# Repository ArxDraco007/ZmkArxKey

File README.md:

# ArxKey - A Custom Split Keyboard

## Building a custom wireless split mechanical keyboard from scratch.

## Why did I make this project?
  There are a lot of ill effects of using a non-ergonomic keyboard. Some basic effects happen, such as ulnar deviation (bending wrists outward), forearm pronation (palms facing down), and unnatural extension. It might also get very serious if you have Carpal Tunnel Syndrome (CTS): The median nerve in the wrist is compressed, often due to swollen tendons. It leads to numbness, tingling, and weakened grip strength. As the times change, you will require a keyboard as it becomes an integral part of your everyday life. It is best to have an ergonomic (furniture or equipment that makes it comfortable and effective for people who use it) keyboard, to make sure you enjoy your work.
You can also type very fast. It is also a very fun project to make, and it is also very cool to have your own custom keyboard (split one too).
### PICTURES!!!
The easy part -

The not-so-easy part - 

fusio' - 

## Assembly instructions - 
1. Heat-press the brass inserts into the case and glue the magnets into place.
2. Screw the stabilizers into the PCB and mount the sliding switch to the case.
3. Solder the diodes, Hall sensors, and header pins to the Seeeduino and PCB.
4. Connect the battery wires to the BAT pins and the sliding power switch.
5. Tuck the battery into its cavity and screw the PCB into the case.
6. Click switches into the plate, screw the plate to the case, and add keycaps.
7. Flash your ZMK firmware to the Seeeduino.
8. Repeat for the second half, pair them, and test your work.
   
## How to use it?
1. Power on both halves, the keyboard will show as ArxSplit in the PC/Phone's Bluetooth settings.
2. The right and left layers are in the general QWERTY layout.
3. Plug the USB-C port into your PC or a charger. The XIAO powers on immediately and also charges the LiPo battery connected to the BAT/VBAT pads.
4. Flashing Firmware - Push the ZMK Files/ directory to a GitHub repo.
5. It will build two .uf2 files, my_keyboard_left and my_keyboard_right.
6. Double-tap the Reset button on the XIAO — it enters bootloader mode and mounts as a USB drive called XIAO-SENSE or NRF52BOOT. Drag and drop the .uf2 file onto that drive. It flashes automatically and reboots.

## Zine!

| Name                           | Purpose                                          | Quantity | Total Cost (USD) | Link                                                                                                                                                                                         | Distributor |
| :----------------------------- | :----------------------------------------------- | :------: | :--------------: | :------------------------------------------------------------------------------------------------------------------------------------------------------------------------------------------- | :---------- |
| **Hotswap Socket**             | Fittings for the Cherry MX                       |    50    |       6.00       | [https://stackskb.com/store/gateron-hotswap-sockets/](https://stackskb.com/store/gateron-hotswap-sockets/)                                                                                   | Stackskb    |
| **Seeed XIAO nRF52840**        | Must be the nRF52840 version for Bluetooth       |     2    |       32.00      | [https://makerbazar.in/products/seeed-studio-xiao-esp32s3-2-4ghz-wifi-ble-5-0](https://www.mouser.in/ProductDetail/Seeed-Studio/102010448?qs=Znm5pLBrcAJ5g%252BWAkitg4w%3D%3D&mgh=1&srsltid=AfmBOookTzqLpFXL5ZJK-A9C8BAJeETLAgGSwWRBi-OlQGBi2qX4YWWgBEQ)                                 | MakerBazar  |
| **LiPo Battery (3.7V)**        | Battery for powering wireless. |     2    |       6.00       | [https://www.electropi.in/3.7v-300mah-lipo-battery-model-401230-india](https://www.electropi.in/3.7v-300mah-lipo-battery-model-401230-india)                                                 | Electropi   |
| **Diodes (1N4148W)**           |   Diodes for core functionality.   |    100   |       1.50       | [https://robu.in/product/1n4148w-slkor-75v-1v-4ns-150ma-sod-123-switching-diodes-rohs](https://robu.in/product/1n4148w-slkor-75v-1v-4ns-150ma-sod-123-switching-diodes-rohs)                 | Robu        |
| **Cherry MX Switches**         | Cherry MX switches are the industry standard for mechanical keyboards                                        |    45    |       18.75      | [https://meckeys.com/shop/accessories/keyboard-accessories/key-switches/cherry-mx-rgb-switch/](https://meckeys.com/shop/accessories/keyboard-accessories/key-switches/cherry-mx-rgb-switch/) | Meckeys     |
| **Resistors** | resistors for core functionality    |     1    |       2.00       | [https://robu.in/product/1k-ohm-1-4w-0805-surface-mount-chip-resistor-pack-of-10](https://robu.in/product/1k-ohm-1-4w-0805-surface-mount-chip-resistor-pack-of-10)                           | Robu        |
| **Custom PCB (JLCPCB)**        | $2 for boards + ~$8 global shipping              |     1    |       10.00      | [https://jlcpcb.com/](https://jlcpcb.com/)                                                                                                                                                   | JLCPCB      | 
| **TOTAL**                      |                                                  |          |     **76.25**    |                                                                                                                                                                                              |             |

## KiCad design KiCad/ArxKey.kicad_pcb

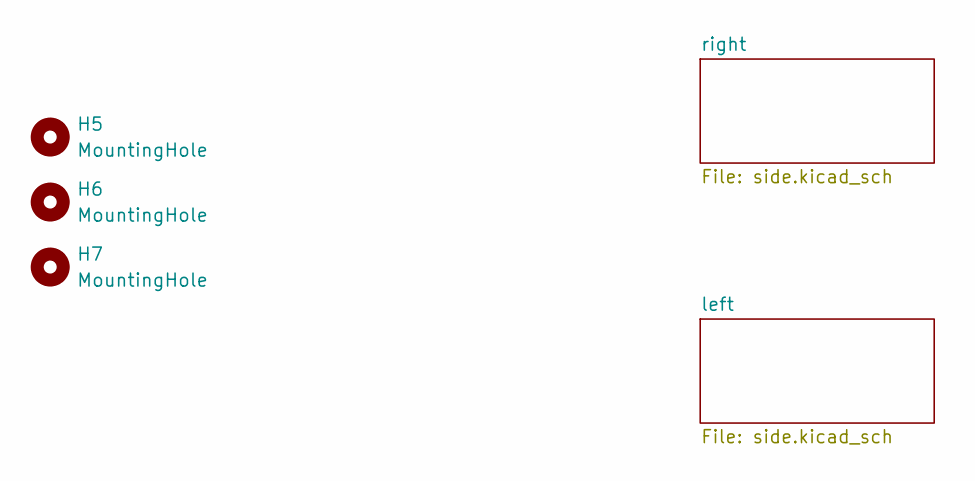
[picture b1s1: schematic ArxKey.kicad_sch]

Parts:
H5, H6, H7: MountingHole; mouse-bite-2mm-slot

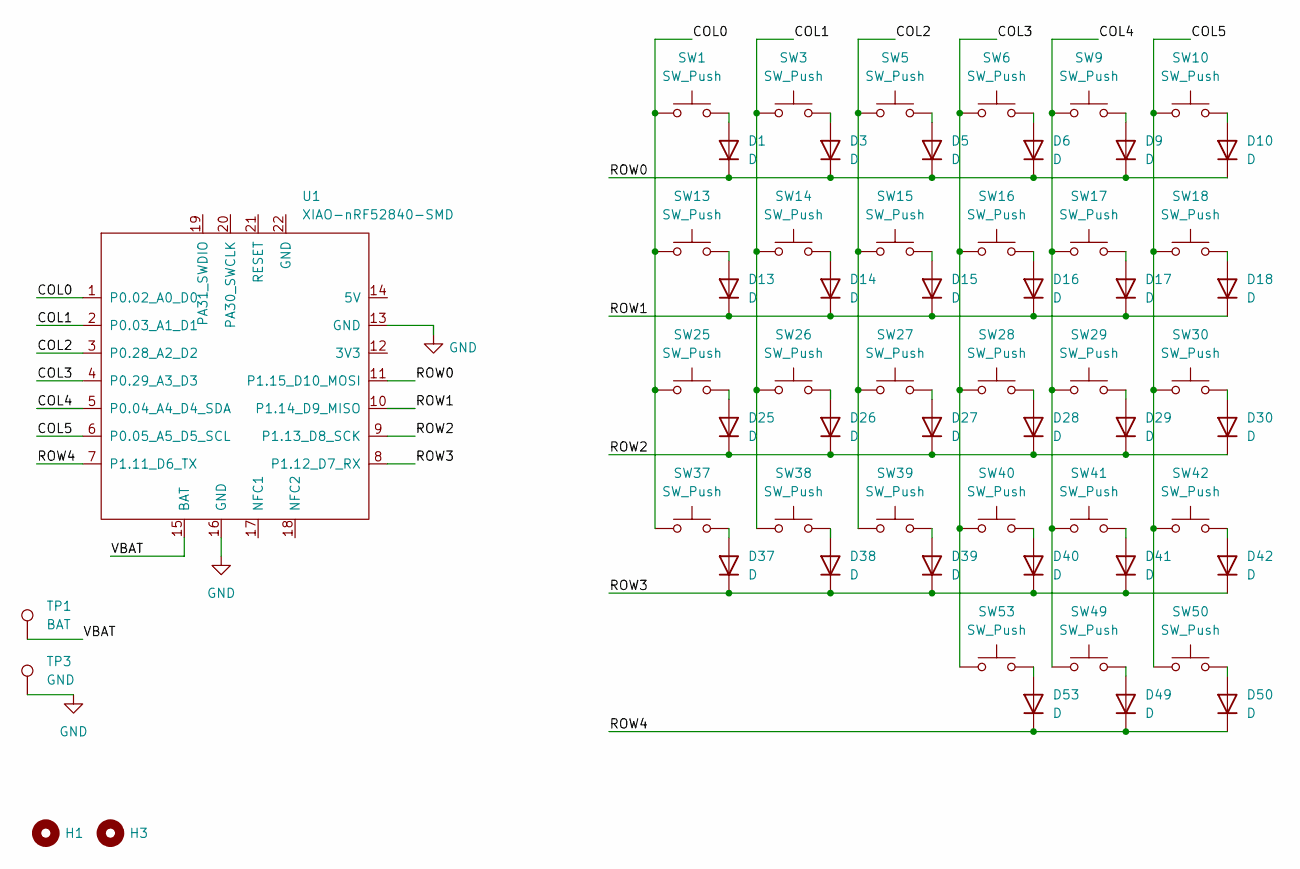
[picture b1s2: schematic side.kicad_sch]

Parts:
D1, D3, D5, D6, D9, D10, D13, D14, D15, D16, D17, D18, D25, D26, D27, D28, D29, D30, D37, D38, D39, D40, D41, D42, D49, D50, D53: D; D_SOD-123
H1, H3: MountingHole; MountingHole_3.2mm_M3
SW1, SW3, SW5, SW6, SW9, SW10, SW13, SW14, SW15, SW16, SW17, SW18, SW25, SW26, SW27, SW28, SW29, SW30, SW37, SW38, SW39, SW40, SW41, SW42, SW49, SW50, SW53: SW_Push; SW_MX_HS_KS-2P02B01-01_1u
TP1: BAT; TestPoint_Pad_D2.0mm
TP3: GND; TestPoint_Pad_D2.0mm
U1: XIAO-nRF52840-SMD; modified-XIAO-nRF52840-SMD

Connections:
/left/COL0: SW1.1, SW13.1, SW25.1, SW37.1, U1.1 (P0.02_A0_D0)
/left/COL1: SW3.1, SW14.1, SW26.1, SW38.1, U1.2 (P0.03_A1_D1)
/left/COL2: SW5.1, SW15.1, SW27.1, SW39.1, U1.3 (P0.28_A2_D2)
/left/COL3: SW6.1, SW16.1, SW28.1, SW40.1, SW53.1, U1.4 (P0.29_A3_D3)
/left/COL4: SW9.1, SW17.1, SW29.1, SW41.1, SW49.1, U1.5 (P0.04_A4_D4_SDA)
/left/COL5: SW10.1, SW18.1, SW30.1, SW42.1, SW50.1, U1.6 (P0.05_A5_D5_SCL)
/left/ROW0: D1.1 (K), D3.1 (K), D5.1 (K), D6.1 (K), D9.1 (K), D10.1 (K), U1.11 (P1.15_D10_MOSI)
/left/ROW1: D13.1 (K), D14.1 (K), D15.1 (K), D16.1 (K), D17.1 (K), D18.1 (K), U1.10 (P1.14_D9_MISO)
/left/ROW2: D25.1 (K), D26.1 (K), D27.1 (K), D28.1 (K), D29.1 (K), D30.1 (K), U1.9 (P1.13_D8_SCK)
/left/ROW3: D37.1 (K), D38.1 (K), D39.1 (K), D40.1 (K), D41.1 (K), D42.1 (K), U1.8 (P1.12_D7_RX)
/left/ROW4: D49.1 (K), D50.1 (K), D53.1 (K), U1.7 (P1.11_D6_TX)
/left/VBAT: TP1.1 (1_1), U1.15 (BAT)
GND: TP3.1 (1_1), U1.13 (GND), U1.16 (GND); also elsewhere on the board
unnamed: D1.2 (A), SW1.2
unnamed: D3.2 (A), SW3.2
unnamed: D5.2 (A), SW5.2
unnamed: D6.2 (A), SW6.2
unnamed: D9.2 (A), SW9.2
unnamed: D10.2 (A), SW10.2
unnamed: D13.2 (A), SW13.2
unnamed: D14.2 (A), SW14.2
unnamed: D15.2 (A), SW15.2
unnamed: D16.2 (A), SW16.2
unnamed: D17.2 (A), SW17.2
unnamed: D18.2 (A), SW18.2
unnamed: D25.2 (A), SW25.2
unnamed: D26.2 (A), SW26.2
unnamed: D27.2 (A), SW27.2
unnamed: D28.2 (A), SW28.2
unnamed: D29.2 (A), SW29.2
unnamed: D30.2 (A), SW30.2
unnamed: D37.2 (A), SW37.2
unnamed: D38.2 (A), SW38.2
unnamed: D39.2 (A), SW39.2
unnamed: D40.2 (A), SW40.2
unnamed: D41.2 (A), SW41.2
unnamed: D42.2 (A), SW42.2
unnamed: D49.2 (A), SW49.2
unnamed: D50.2 (A), SW50.2
unnamed: D53.2 (A), SW53.2

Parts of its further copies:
D2, D4, D7, D8, D11, D12, D19, D20, D21, D22, D23, D24, D31, D32, D33, D34, D35, D36, D43, D44, D45, D46, D47, D48, D51, D52, D54: D; D_SOD-123
H2, H4: MountingHole; MountingHole_3.2mm_M3
SW2, SW4, SW7, SW8, SW11, SW12, SW19, SW20, SW21, SW22, SW23, SW24, SW31, SW32, SW33, SW34, SW35, SW36, SW43, SW44, SW45, SW46, SW47, SW48, SW51, SW52, SW54: SW_Push; SW_MX_HS_KS-2P02B01-01_1u
TP2: BAT; TestPoint_Pad_D2.0mm
TP4: GND; TestPoint_Pad_D2.0mm
U2: XIAO-nRF52840-SMD; modified-XIAO-nRF52840-SMD

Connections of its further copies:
/right/COL0: SW2.1, SW19.1, SW31.1, SW43.1, U2.1 (P0.02_A0_D0)
/right/COL1: SW4.1, SW20.1, SW32.1, SW44.1, U2.2 (P0.03_A1_D1)
/right/COL2: SW7.1, SW21.1, SW33.1, SW45.1, U2.3 (P0.28_A2_D2)
/right/COL3: SW8.1, SW22.1, SW34.1, SW46.1, SW54.1, U2.4 (P0.29_A3_D3)
/right/COL4: SW11.1, SW23.1, SW35.1, SW47.1, SW51.1, U2.5 (P0.04_A4_D4_SDA)
/right/COL5: SW12.1, SW24.1, SW36.1, SW48.1, SW52.1, U2.6 (P0.05_A5_D5_SCL)
/right/ROW0: D2.1 (K), D4.1 (K), D7.1 (K), D8.1 (K), D11.1 (K), D12.1 (K), U2.11 (P1.15_D10_MOSI)
/right/ROW1: D19.1 (K), D20.1 (K), D21.1 (K), D22.1 (K), D23.1 (K), D24.1 (K), U2.10 (P1.14_D9_MISO)
/right/ROW2: D31.1 (K), D32.1 (K), D33.1 (K), D34.1 (K), D35.1 (K), D36.1 (K), U2.9 (P1.13_D8_SCK)
/right/ROW3: D43.1 (K), D44.1 (K), D45.1 (K), D46.1 (K), D47.1 (K), D48.1 (K), U2.8 (P1.12_D7_RX)
/right/ROW4: D51.1 (K), D52.1 (K), D54.1 (K), U2.7 (P1.11_D6_TX)
/right/VBAT: TP2.1 (1_1), U2.15 (BAT)
GND: TP4.1 (1_1), U2.13 (GND), U2.16 (GND); also elsewhere on the board
unnamed: D2.2 (A), SW2.2
unnamed: D4.2 (A), SW4.2
unnamed: D7.2 (A), SW7.2
unnamed: D8.2 (A), SW8.2
unnamed: D11.2 (A), SW11.2
unnamed: D12.2 (A), SW12.2
unnamed: D19.2 (A), SW19.2
unnamed: D20.2 (A), SW20.2
unnamed: D21.2 (A), SW21.2
unnamed: D22.2 (A), SW22.2
unnamed: D23.2 (A), SW23.2
unnamed: D24.2 (A), SW24.2
unnamed: D31.2 (A), SW31.2
unnamed: D32.2 (A), SW32.2
unnamed: D33.2 (A), SW33.2
unnamed: D34.2 (A), SW34.2
unnamed: D35.2 (A), SW35.2
unnamed: D36.2 (A), SW36.2
unnamed: D43.2 (A), SW43.2
unnamed: D44.2 (A), SW44.2
unnamed: D45.2 (A), SW45.2
unnamed: D46.2 (A), SW46.2
unnamed: D47.2 (A), SW47.2
unnamed: D48.2 (A), SW48.2
unnamed: D51.2 (A), SW51.2
unnamed: D52.2 (A), SW52.2
unnamed: D54.2 (A), SW54.2

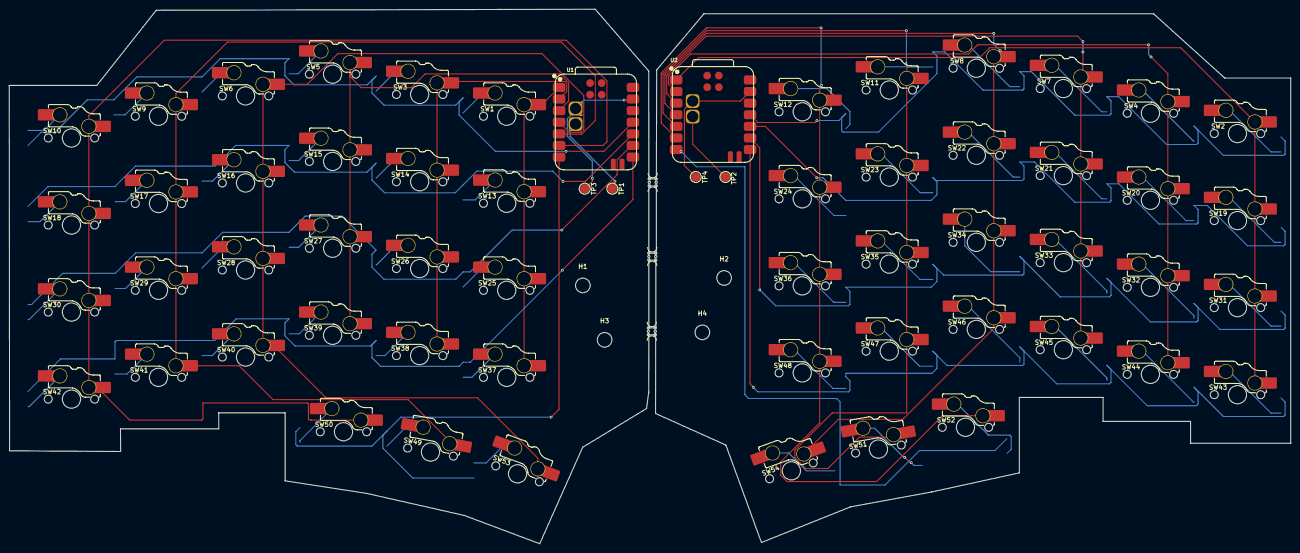
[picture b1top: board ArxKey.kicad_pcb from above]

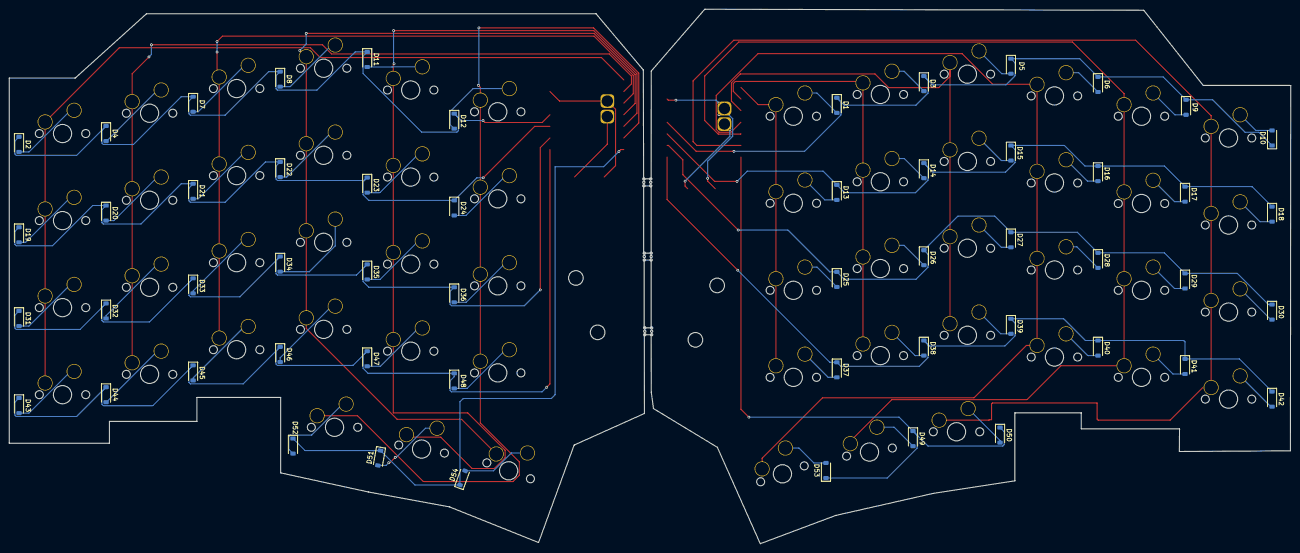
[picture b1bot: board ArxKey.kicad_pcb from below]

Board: 2 copper layers, 280.5 x 117.0 mm, 121 parts (54 on the bottom side), 79 nets.

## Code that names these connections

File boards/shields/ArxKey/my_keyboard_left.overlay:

#include "my_keyboard.dtsi"

&kscan0 {
    col-gpios
        = <&xiao_d 0 GPIO_ACTIVE_HIGH> // COL0
        , <&xiao_d 1 GPIO_ACTIVE_HIGH> // COL1
        , <&xiao_d 2 GPIO_ACTIVE_HIGH> // COL2
        , <&xiao_d 3 GPIO_ACTIVE_HIGH> // COL3
        , <&xiao_d 4 GPIO_ACTIVE_HIGH> // COL4
        , <&xiao_d 5 GPIO_ACTIVE_HIGH> // COL5
        ;

    row-gpios
        = <&xiao_d 10 (GPIO_ACTIVE_HIGH | GPIO_PULL_DOWN)> // ROW0
        , <&xiao_d 9  (GPIO_ACTIVE_HIGH | GPIO_PULL_DOWN)> // ROW1
        , <&xiao_d 8  (GPIO_ACTIVE_HIGH | GPIO_PULL_DOWN)> // ROW2
        , <&xiao_d 7  (GPIO_ACTIVE_HIGH | GPIO_PULL_DOWN)> // ROW3
        , <&xiao_d 6  (GPIO_ACTIVE_HIGH | GPIO_PULL_DOWN)> // ROW4
        ;
};

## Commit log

2026-04-12 Add Kconfig for ArxKey keyboard shields
2026-04-12 Add your_keyboard.dtsi for ArxKey shield configuration
2026-04-12 Kicad Files!
    Adding PCB and schematics
2026-04-12 Add KiCad footprints, 3D models, and symbols
    Add multiple KiCad library items for PCB design: 3D models (D_SOD-123, MountingHole_2.2mm_M2, MouseBite-Part_2.0x2.0mm... Trace), footprints (mouse-bite-2mm-slot, modified XIAO-nRF52840-SMD, SW_MX_HE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
2026-04-12 Create ArxKey-bom.csv
    BOM file
2026-04-12 Create README for custom split keyboard project
    Added a README file detailing the project for a custom wireless split mechanical keyboard, including a bill of materials and images.
2026-04-12 Update README with assembly instructions
    Added assembly instructions for building the keyboard.
2026-05-02 Organizing
2026-05-02 PCB Updates
2026-05-02 Zine Changes
2026-05-04 Changes in README and CAD updates.
2026-05-05 stp files and 3mf files
2026-05-05 CAD Design added
2026-05-24 zine and pcbv
2026-05-24 Update README with new images and assembly steps
    Added additional images and assembly instructions to the README.
2026-06-03 build fixing
2026-06-03 Rename project to ArxKey and add usage section
    Updated project name and added usage section with zine link.
2026-06-03 Gerber
2026-06-03 Update README with usage instructions
    Added usage instructions for the keyboard setup and firmware flashing.
2026-06-04 splitkeyboard.step
2026-06-04 gerber and drill
2026-06-04 Add 1.5V LED Bulbs to components list
2026-06-05 step
2026-06-05 assembly change
2026-06-05 step file
